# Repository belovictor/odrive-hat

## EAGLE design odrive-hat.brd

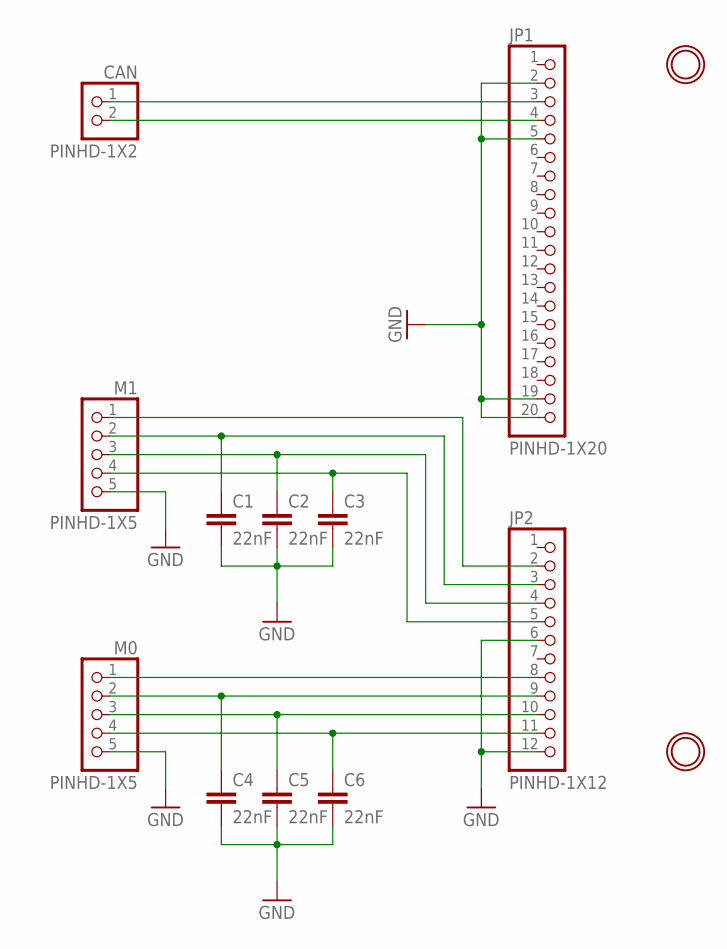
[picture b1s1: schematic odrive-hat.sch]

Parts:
C1, C2, C3, C4, C5, C6: 22nF; C0603
CAN: PINHD-1X2; 1X02
JP1: PINHD-1X20; 1X20
JP2: PINHD-1X12; 1X12
M0, M1: PINHD-1X5; 1X05
U$1, U$2: MICROBUILDER_MOUNTINGHOLE3.0THIN; MICROBUILDER_MOUNTINGHOLE_3.0_PLATEDTHIN

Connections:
GND: C1.2, C2.2, C3.2, C4.2, C5.2, C6.2, JP1.2, JP1.5, JP1.19, JP1.20, JP2.6, JP2.12, M0.5, M1.5
unnamed: CAN.1, JP1.3
unnamed: CAN.2, JP1.4
unnamed: C3.1, JP2.5, M1.4
unnamed: C2.1, JP2.4, M1.3
unnamed: C6.1, JP2.11, M0.4
unnamed: C5.1, JP2.10, M0.3
unnamed: C4.1, JP2.9, M0.2
unnamed: JP2.8, M0.1
unnamed: C1.1, JP2.3, M1.2
unnamed: JP2.2, M1.1

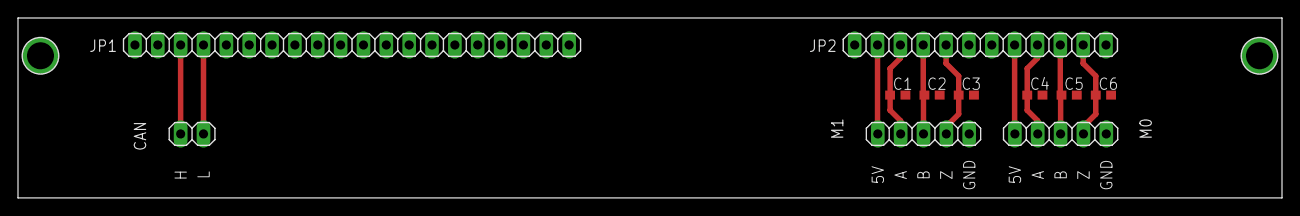
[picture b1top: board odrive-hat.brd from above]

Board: 2 copper layers, 140.5 x 20.0 mm, 13 parts (0 on the bottom side), 11 nets.
